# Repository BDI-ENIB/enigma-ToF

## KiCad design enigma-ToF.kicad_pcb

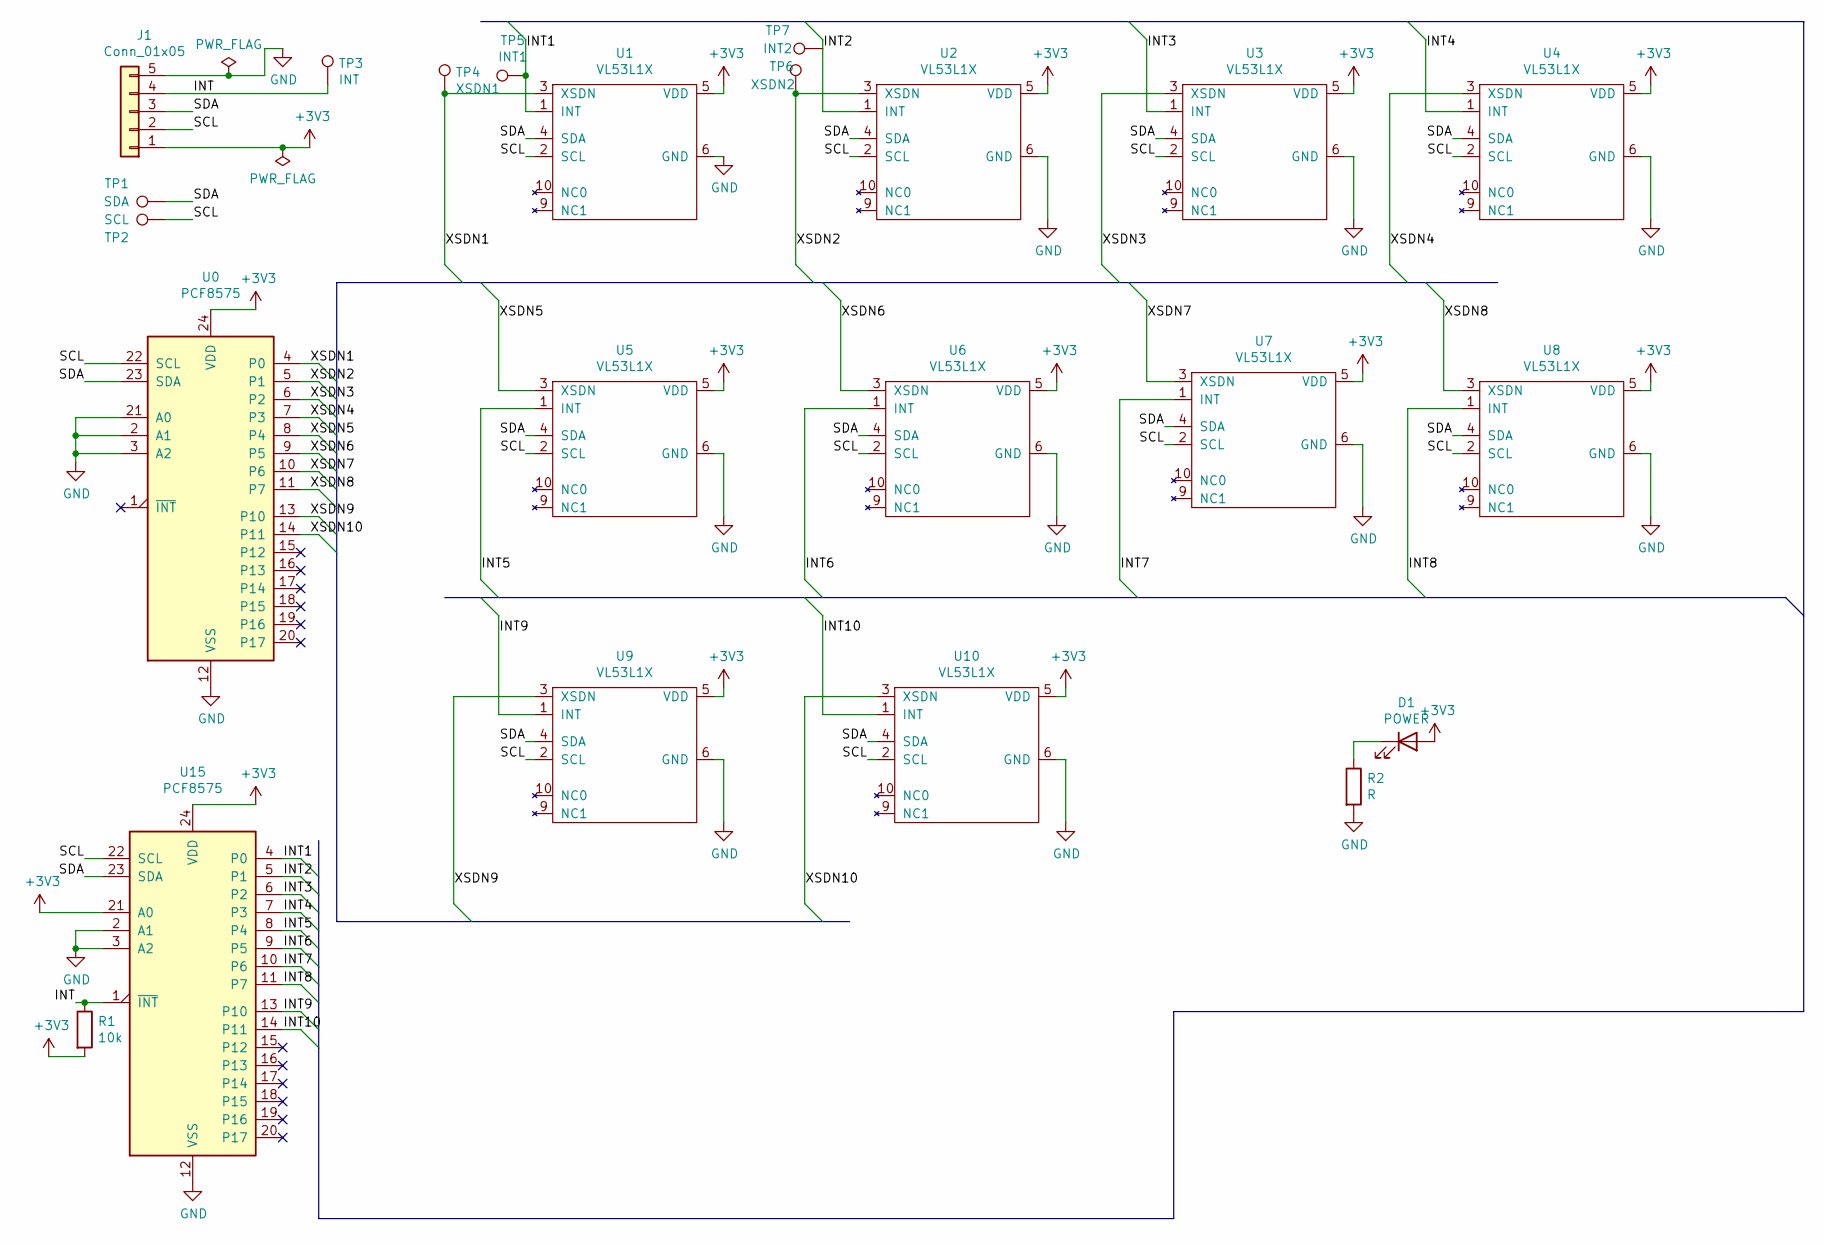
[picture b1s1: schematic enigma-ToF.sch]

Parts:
D1: POWER; LED_PLCC-2
J1: Conn_01x05; Molex_KK-254_AE-6410-05A_1x05_P2.54mm_Vertical
R1: 10k; R_1206_3216Metric_Pad1.42x1.75mm_HandSolder
R2: R; R_1206_3216Metric_Pad1.42x1.75mm_HandSolder
TP1: SDA; TestPoint_Loop_D2.54mm_Drill1.5mm_Beaded
TP2: SCL; TestPoint_Loop_D2.54mm_Drill1.5mm_Beaded
TP3: INT; TestPoint_Loop_D2.54mm_Drill1.5mm_Beaded
TP4: XSDN1; TestPoint_Loop_D2.54mm_Drill1.5mm_Beaded
TP5: INT1; TestPoint_Loop_D2.54mm_Drill1.5mm_Beaded
TP6: XSDN2; TestPoint_Loop_D2.54mm_Drill1.5mm_Beaded
TP7: INT2; TestPoint_Loop_D2.54mm_Drill1.5mm_Beaded
U0, U15: PCF8575; SOIC-24W_7.5x15.4mm_P1.27mm
U1, U2, U3, U4, U5, U6, U7, U8, U9, U10: VL53L1X; IDC-Header_2x05_P2.54mm_Vertical

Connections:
+3V3: D1.2 (A), J1.1, R1.2, U0.24 (VDD), U1.5 (VDD), U2.5 (VDD), U3.5 (VDD), U4.5 (VDD), U5.5 (VDD), U6.5 (VDD), U7.5 (VDD), U8.5 (VDD), U9.5 (VDD), U10.5 (VDD), U15.21 (A0), U15.24 (VDD)
/INT: J1.4, R1.1, TP3.1, U15.1 (~INT~)
/INT1: TP5.1, U1.1 (INT), U15.4 (P0)
/INT2: TP7.1, U2.1 (INT), U15.5 (P1)
/INT3: U3.1 (INT), U15.6 (P2)
/INT4: U4.1 (INT), U15.7 (P3)
/INT5: U5.1 (INT), U15.8 (P4)
/INT6: U6.1 (INT), U15.9 (P5)
/INT7: U7.1 (INT), U15.10 (P6)
/INT8: U8.1 (INT), U15.11 (P7)
/INT9: U9.1 (INT), U15.13 (P10)
/INT10: U10.1 (INT), U15.14 (P11)
/SCL: J1.2, TP2.1, U0.22 (SCL), U1.2 (SCL), U2.2 (SCL), U3.2 (SCL), U4.2 (SCL), U5.2 (SCL), U6.2 (SCL), U7.2 (SCL), U8.2 (SCL), U9.2 (SCL), U10.2 (SCL), U15.22 (SCL)
/SDA: J1.3, TP1.1, U0.23 (SDA), U1.4 (SDA), U2.4 (SDA), U3.4 (SDA), U4.4 (SDA), U5.4 (SDA), U6.4 (SDA), U7.4 (SDA), U8.4 (SDA), U9.4 (SDA), U10.4 (SDA), U15.23 (SDA)
/XSDN1: TP4.1, U0.4 (P0), U1.3 (XSDN)
/XSDN2: TP6.1, U0.5 (P1), U2.3 (XSDN)
/XSDN3: U0.6 (P2), U3.3 (XSDN)
/XSDN4: U0.7 (P3), U4.3 (XSDN)
/XSDN5: U0.8 (P4), U5.3 (XSDN)
/XSDN6: U0.9 (P5), U6.3 (XSDN)
/XSDN7: U0.10 (P6), U7.3 (XSDN)
/XSDN8: U0.11 (P7), U8.3 (XSDN)
/XSDN9: U0.13 (P10), U9.3 (XSDN)
/XSDN10: U0.14 (P11), U10.3 (XSDN)
GND: J1.5, R2.2, U0.2 (A1), U0.3 (A2), U0.12 (VSS), U0.21 (A0), U1.6 (GND), U2.6 (GND), U3.6 (GND), U4.6 (GND), U5.6 (GND), U6.6 (GND), U7.6 (GND), U8.6 (GND), U9.6 (GND), U10.6 (GND), U15.2 (A1), U15.3 (A2), U15.12 (VSS)
unnamed: D1.1 (K), R2.1

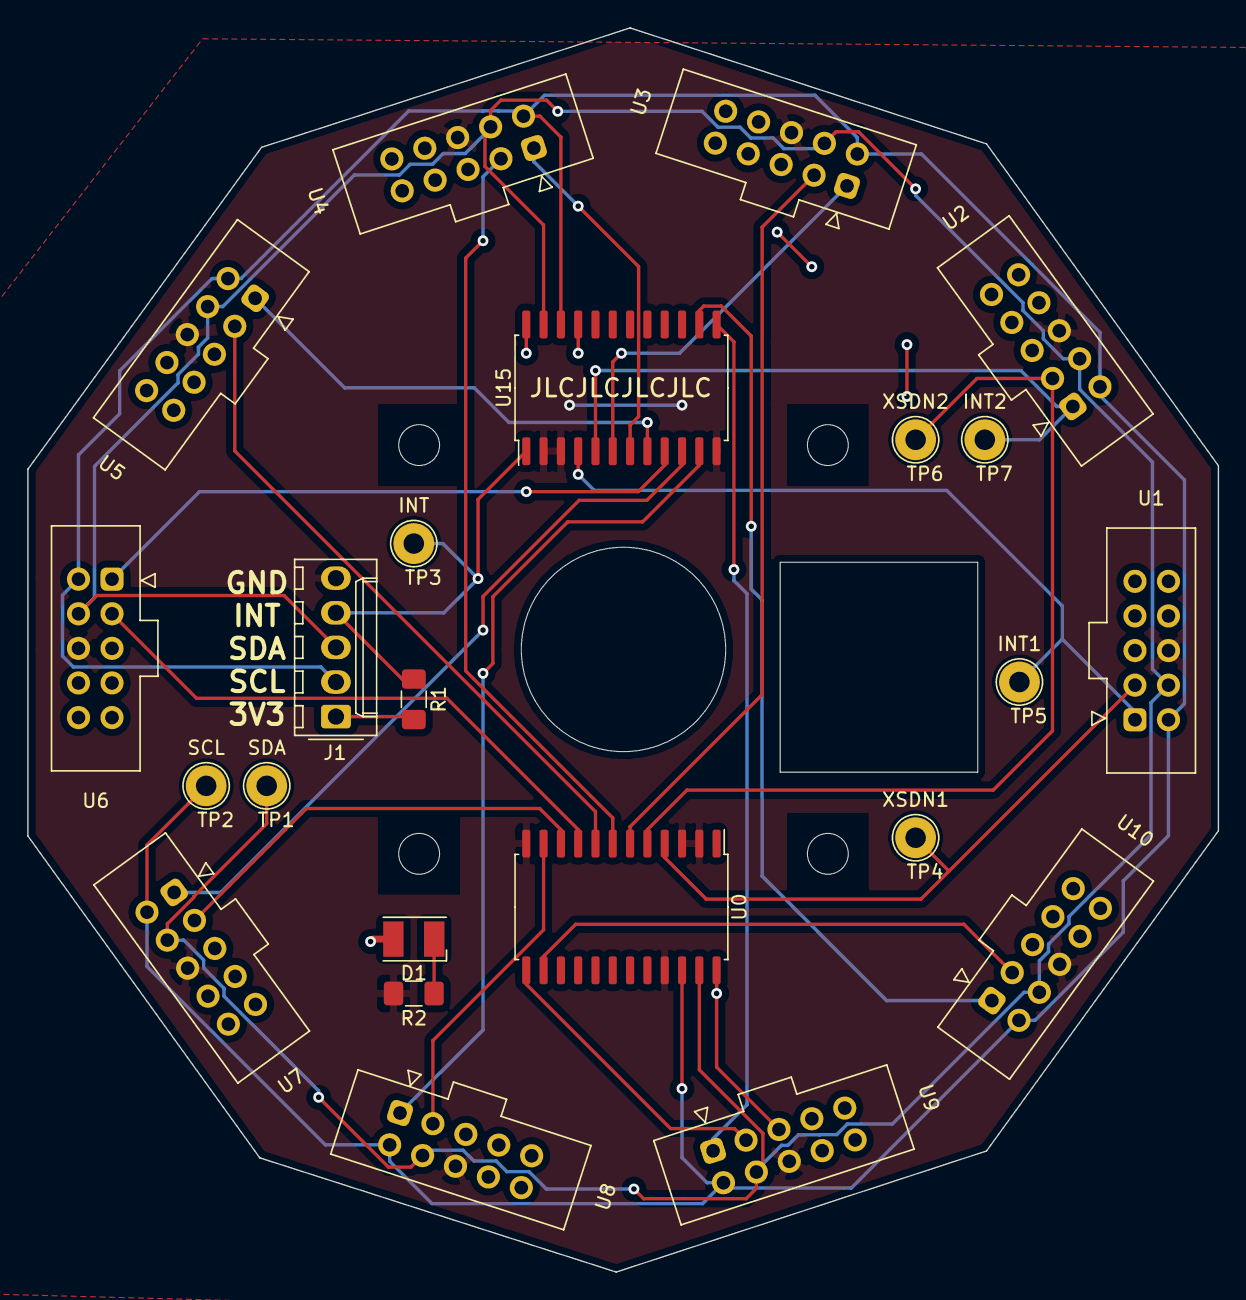
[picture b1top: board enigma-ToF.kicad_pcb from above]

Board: 2 copper layers, 87.4 x 91.3 mm, 23 parts (0 on the bottom side), 26 nets.

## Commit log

2019-12-05 Add ST api for VL53L1X
2019-12-06 Update includes to work in place.
2019-12-09 Update imports in ULD API
2019-12-09 Add Ultra Lite Driver API
2019-12-09 Remove Complete API
    We'll use the ULD API
2019-12-09 Proof of concept with 1 vl53l1x
2019-12-09 Unify case of file names
2019-12-09 PoC Changing address
2020-06-16 Move © notice to end of ST files
2020-06-16 Create class Tof
2020-06-16 Test with two sensors
2020-06-20 Fix boot state checking
2020-06-20 Make it compile
    Forgot a semicolon you dunce
2020-06-20 Add import for i2c_t3 in params to use Wire1
2020-06-20 Remove unneeded led on
2020-06-20 Move general setup in `my_setup`
    Enables the use of Serial output during setup
2020-06-20 Add comment for wait 1s at boot
2020-06-20 Add precompiler switch for serial debug
2020-06-21 Add driver for PCF8575 chip expander
    Not tested
2020-09-10 Add PCB
    Yay !!!
2020-09-10 Add touchpoints and power LED
2020-09-11 Change LED model and generate gerbers
2020-09-11 Add conditional compiling for interrupt mode
2020-09-11 Use references instead of pointers, it's C++
2020-09-21 Round PCB causes collisions let's do decagon
2020-09-21 USB-B port on IRoise was not in the right place...
2020-09-22 Update gerbers
2020-09-30 Add JLCPCB silkscreen
